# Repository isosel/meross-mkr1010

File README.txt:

I would like to apologize in advance for my bad english :3

Source codes are provided within "src" folder.

Documentations, shematics, photos are provided within "doc" folder.

The program named code.ino aims to remotly control a connected Outlet plug in order to switch it ON or OFF, check the wiki for more details. 

It has to be incorporated into the SCAO project "Quiet Cook" made by Régis Leruste.

A big thx to Ilias Nafili for his help in understanding internet protocol and servers ♥ ♥ ♥

More improvement coming soon (low power mode and auto-configuration IP) cause the smart plug often change his IP address, it's boring.

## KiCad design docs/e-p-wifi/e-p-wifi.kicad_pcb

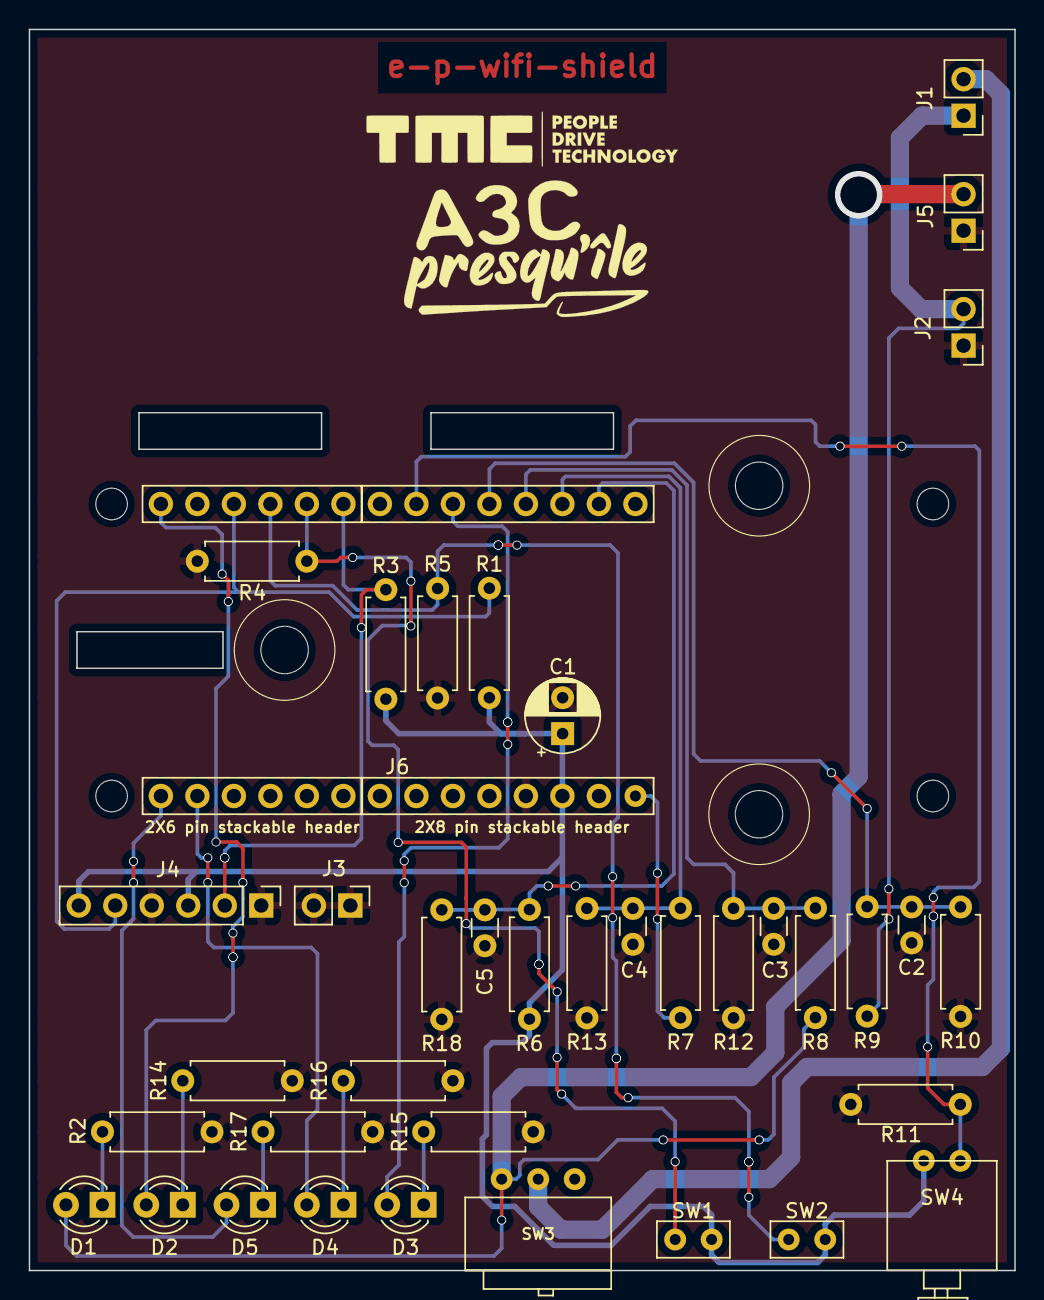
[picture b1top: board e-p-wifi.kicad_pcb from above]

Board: 2 copper layers, 68.6 x 86.4 mm, 38 parts (0 on the bottom side), 24 nets.

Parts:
C1: 4.7µF; CP_Radial_D5.0mm_P2.50mm
C2, C3, C4, C5: 0.1mF; C_Disc_D3.0mm_W1.6mm_P2.50mm
D1: vert; LED_D3.0mm
D2: Vert; LED_D3.0mm
D3: bleu; LED_D3.0mm
D4: Rouge; LED_D3.0mm
D5: Jaune; LED_D3.0mm
J1: Shunt; PinHeader_1x02_P2.54mm_Vertical
J2: Vbat1; PinHeader_1x02_P2.54mm_Vertical
J3: Masse T1; PinHeader_1x02_P2.54mm_Vertical
J4: Température; PinHeader_1x06_P2.54mm_Vertical
J5: Vbat2; PinHeader_1x02_P2.54mm_Vertical
J6: Conn_02x14_MKR1010; PinSocket_2x14_MKR1010
R1, R3, R6, R7, R8, R9, R10, R12, R13, R18: 4.7k; R_Axial_DIN0207_L6.3mm_D2.5mm_P7.62mm_Horizontal
R2, R14, R15, R16, R17: 1K; R_Axial_DIN0207_L6.3mm_D2.5mm_P7.62mm_Horizontal
R4, R5, R11: 47k; R_Axial_DIN0207_L6.3mm_D2.5mm_P7.62mm_Horizontal
SW1: StSp; jumper-switch
SW2: Sleep; jumper-switch
SW3: Conrad 711771; switch
SW4: BP APEM; BP

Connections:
+3V3: C1.1, J4.3, J4.6, J6.+3V3, R1.1, R3.1, R6.1, SW1.1, SW2.1, SW4.1
GND: C1.2, C2.2, C3.2, C4.2, C5.2, J2.1, J3.1, J3.2, J4.1, J4.4, J5.1, J6.GND, R2.1, R4.2, R5.2, R10.2, R11.1, R12.2, R13.2, R14.1, R15.1, R16.1, R17.1, R18.2
unnamed: C2.1, J6.A3, R9.2, R10.1
unnamed: C3.1, J6.A2, R8.2, R12.1
unnamed: C4.1, J6.A1, R7.2, R13.1
unnamed: C5.1, J6.A0, R6.2, R18.1
unnamed: D1.1, R2.2
unnamed: D1.2, J5.2, R8.1, SW3.3
unnamed: D2.1, R14.2
unnamed: D2.2, J6.D5
unnamed: D3.1, R15.2
unnamed: D3.2, J6.A4
unnamed: D4.1, R16.2
unnamed: D4.2, J6.D7
unnamed: D5.1, R17.2
unnamed: D5.2, J6.D6
unnamed: J1.1, J2.2, R9.1
unnamed: J1.2, SW3.2
unnamed: J4.2, J6.D0, R3.2
unnamed: J4.5, J6.D3, R1.2
unnamed: J6.+5V, R7.1
unnamed: J6.A5, R11.2, SW4.2
unnamed: J6.D1, R4.1, SW1.2
unnamed: J6.D2, R5.1, SW2.2

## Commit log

2019-11-06 Update code.ino
    improvment
2019-11-08 pull1
    blabla
2019-12-07 kikad document
2019-12-07 kikad docs
2019-12-07 docs
2019-12-10 update 10/12/2019 Kicad Files
2019-12-10 test
2019-12-10 Update 10-12-2019 Kicad Files
2019-12-10 Update Kicad Files 10-12-2019 LED position and SW3 footprint
2019-12-12 add picture
2019-12-12 add symbol picture
2019-12-12 add eeschema picture
2019-12-12 add pcbnew icon picture
2019-12-12 add net icon
2019-12-12 add files
2019-12-12 ededeed
2019-12-12 dedede
2019-12-12 add pcb cotation
2019-12-13 mise à jour des fichiers Kicad pour etre compliant avec le fournisseur
2019-12-16 photos added
2019-12-16 add photos
2019-12-17 add comments to code.ino
2019-12-17 add temp-coord-hole picture
2019-12-17 add 2 photo for clamp cable holes
2019-12-17 additional info for mkr1010 and holes location
2019-12-17 mounting hole location picture added
2019-12-17 circle icon picture added
2019-12-17 mm icon added
2019-12-17 hole location and placement finish
2019-12-17 chevelu icon added
2019-12-17 mkr1010-placement.PNG added
2019-12-18 add picture for 1st component placement
2019-12-30 suppression du dossier old
2019-12-31 add pictures
2020-01-13 mis à jour du code pour la prise de Régis
